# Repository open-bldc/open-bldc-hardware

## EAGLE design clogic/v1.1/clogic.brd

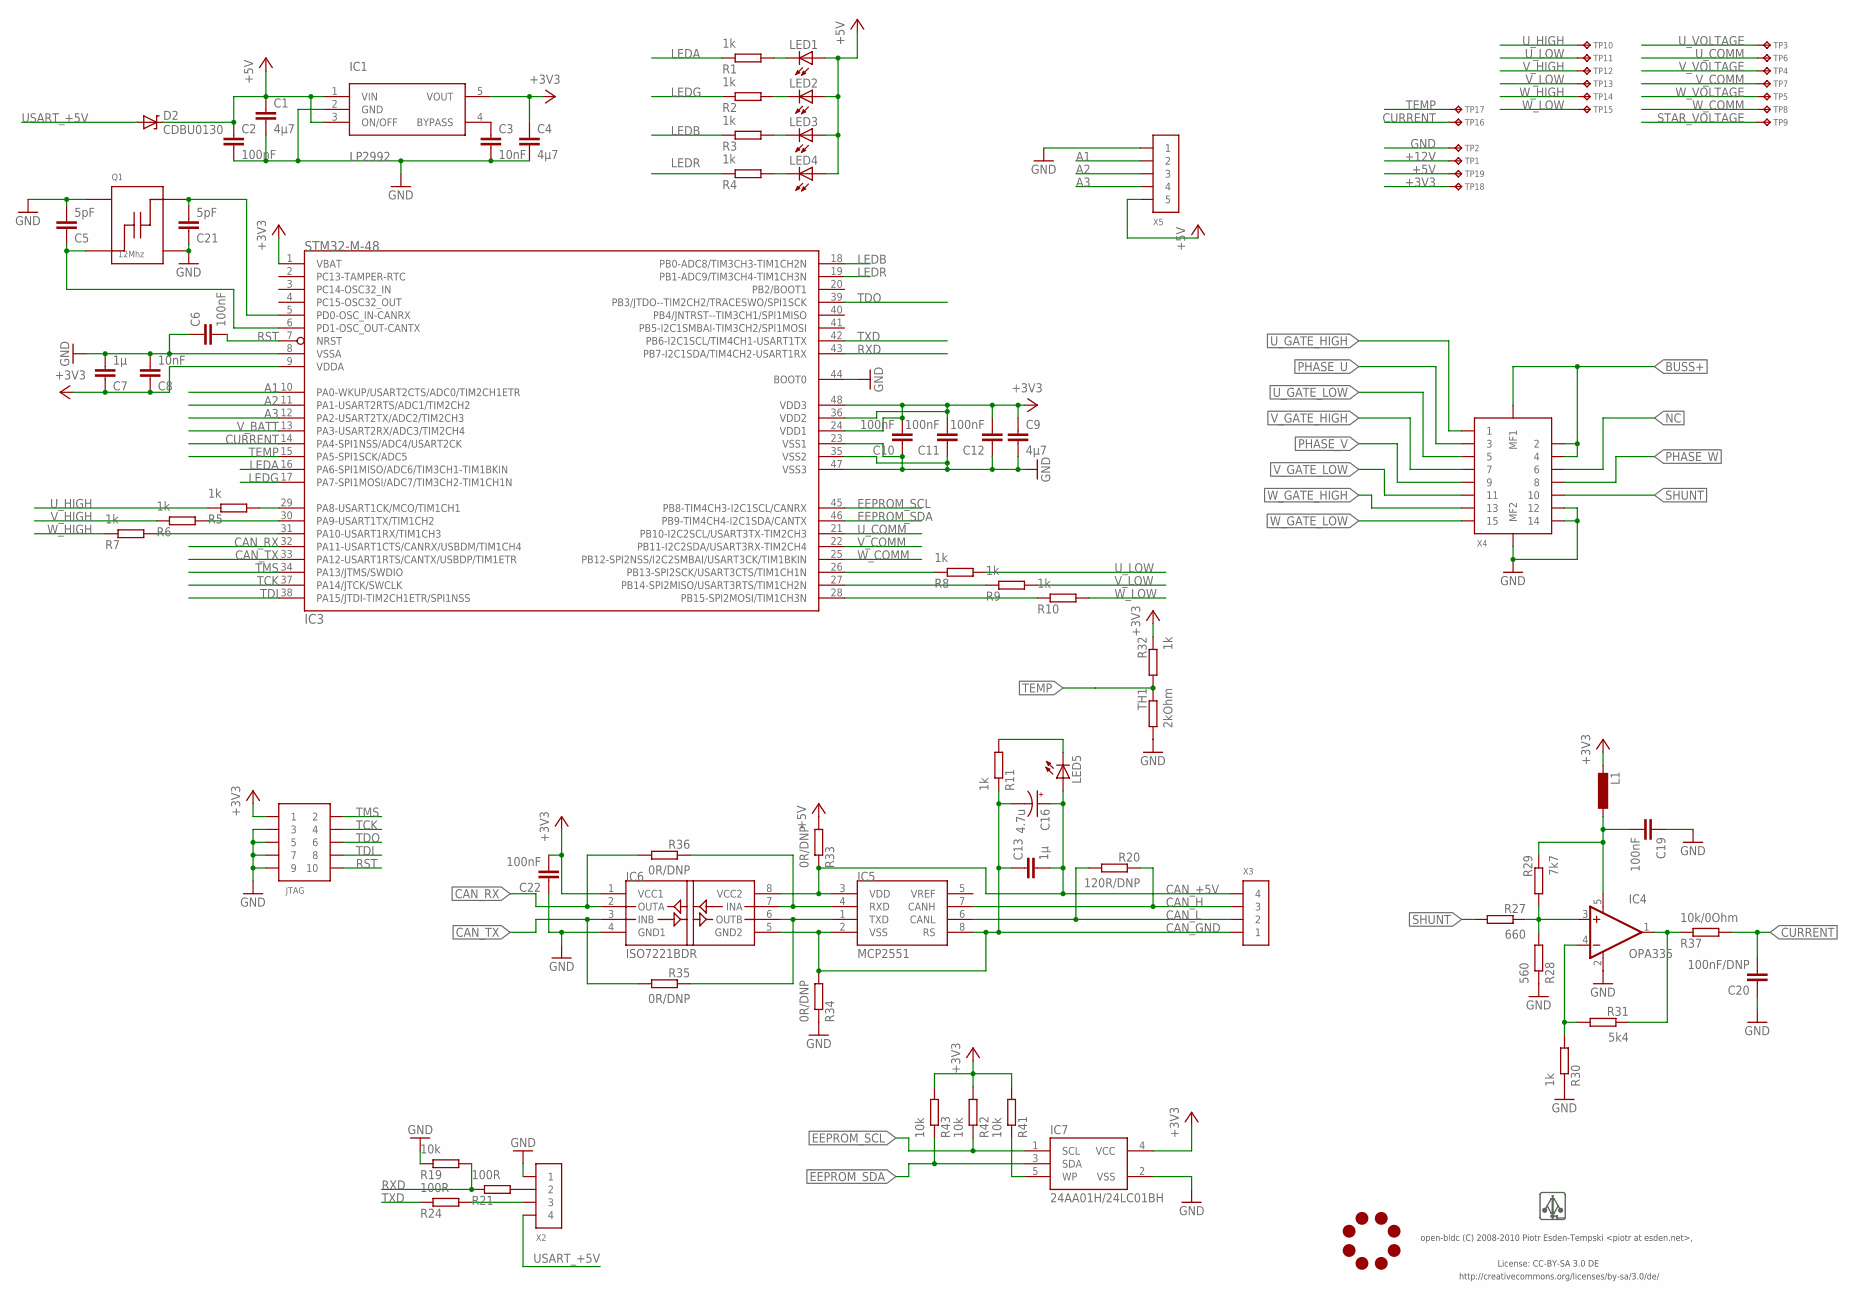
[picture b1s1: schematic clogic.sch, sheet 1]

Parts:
C1, C4, C9: 4µ7; 0603-CAP
C2, C6, C10, C11, C12, C19, C22: 100nF; 0603-CAP
C3, C8: 10nF; 0603-CAP
C5, C21: 5pF; 0603-CAP
C7, C13: 1µ; 0603-CAP
C16: 4.7u; CAP_0805TANT_F95
C20: 100nF/DNP; 0603-CAP
D2: CDBU0130; 0603-LED
IC1: LP2992; SOT23-5
IC3: STM32-M-48; LQFP48
IC4: OPA335; SOT23-5
IC5: MCP2551; SO8
IC6: ISO7221BDR; SO8
IC7: 24AA01H/24LC01BH; SOT23-5
JL1: JOBY_LOGO-6MIL; JOBY_LOGO_6MIL
JTAG: CONN_5-2-FTSH-V; FTSH-105-DV
L1: INDUCTOR-0603; 0603-IND
LED1: AMBER; 0603-LED
LED2: GREEN; 0603-LED
LED3: BLUE; 0603-LED
LED4: RED; 0603-LED
LED5: WHITE; 0603-LED
Q1: 12Mhz; ABM8
R1, R2, R3, R4, R5, R6, R7, R8, R9, R10, R11, R30, R32: 1k; 0603-RES
R19, R41, R42, R43: 10k; 0603-RES
R20: 120R/DNP; 0603-RES
R21, R24: 100R; 0603-RES
R27: 660; 0603-RES
R28: 560; 0603-RES
R29: 7k7; 0603-RES
R31: 5k4; 0603-RES
R33, R34, R35, R36: 0R/DNP; 0603-RES
R37: 10k/0Ohm; 0603-RES
TH1: 2kOhm; 0603-RES
TP1, TP2, TP3, TP4, TP5, TP6, TP7, TP8, TP9, TP10, TP11, TP12, TP13, TP14, TP15, TP16, TP17, TP18, TP19: TP-09RSMD; TP09R
U$1: LOGO
X2, X3: CONN_4-1-53261; PB-53261-04
X4: CONN_15-2-2MT-DF9; DF9-15
X5: CONN_5-1-53261; PB-53261-05

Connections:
+3V3: C4.P$1 (1), C7.P$1 (1), C8.P$1 (1), C9.P$1 (1), C10.P$2 (2), C11.P$2 (2), C12.P$2 (2), C22.P$2 (2), IC1.5 (VOUT), IC3.1 (VBAT), IC3.9 (VDDA), IC3.24 (VDD1), IC3.36 (VDD2), IC3.48 (VDD3), IC6.1 (VCC1), IC7.4 (VCC), JTAG.1, L1.P$2 (2), R32.P$1 (1), R41.P$2 (2), R42.P$2 (2), R43.P$2 (2), TP18.P$1
+5V: C1.P$1 (1), C2.P$1 (1), D2.C, IC1.1 (VIN), IC1.3 (ON/OFF), LED1.A, LED2.A, LED3.A, LED4.A, R33.P$2 (2), TP19.P$1, X5.5; also elsewhere on the board
+12V: TP1.P$1; also elsewhere on the board
A1: IC3.10 (PA0-WKUP/USART2CTS/ADC0/TIM2CH1ETR), X5.2; also elsewhere on the board
A2: IC3.11 (PA1-USART2RTS/ADC1/TIM2CH2), X5.3; also elsewhere on the board
A3: IC3.12 (PA2-USART2TX/ADC2/TIM2CH3), X5.4; also elsewhere on the board
BUSS+: X4.2, X4.4, X4.MF1; also elsewhere on the board
CAN_+5V: C13.P$2 (2), C16.P$1 (+), IC5.3 (VDD), IC6.8 (VCC2), LED5.A, R33.P$1 (1), X3.4
CAN_GND: C13.P$1 (1), C16.P$2 (-), IC5.2 (VSS), IC5.8 (RS), IC6.5 (GND2), R11.P$1 (1), R34.P$2 (2), X3.1
CAN_H: IC5.7 (CANH), R20.P$1 (1), X3.3
CAN_L: IC5.6 (CANL), R20.P$2 (2), X3.2
CAN_RX: IC3.32 (PA11-USART1CTS/CANRX/USBDM/TIM1CH4), IC6.2 (OUTA), R36.P$2 (2)
CAN_TX: IC3.33 (PA12-USART1RTS/CANTX/USBDP/TIM1ETR), IC6.3 (INB), R35.P$2 (2)
CURRENT: C20.P$2 (2), IC3.14 (PA4-SPI1NSS/ADC4/USART2CK), R37.P$2 (2), TP16.P$1
CURRENT_RAW: IC4.1 (OUT), R31.P$1 (1), R37.P$1 (1)
EEPROM_SCL: IC3.45 (PB8-TIM4CH3-I2C1SCL/CANRX), IC7.1 (SCL), R42.P$1 (1)
EEPROM_SDA: IC3.46 (PB9-TIM4CH4-I2C1SDA/CANTX), IC7.3 (SDA), R43.P$1 (1)
GND: C1.P$2 (2), C2.P$2 (2), C3.P$2 (2), C4.P$2 (2), C5.P$2 (2), C6.P$1 (1), C7.P$2 (2), C8.P$2 (2), C9.P$2 (2), C10.P$1 (1), C11.P$1 (1), C12.P$1 (1), C19.P$1 (1), C20.P$1 (1), C21.P$1 (1), C22.P$1 (1), IC1.2 (GND), IC3.8 (VSSA), IC3.23 (VSS1), IC3.35 (VSS2), IC3.44 (BOOT0), IC3.47 (VSS3), IC4.2 (V-), IC6.4 (GND1), IC7.2 (VSS), JTAG.3, JTAG.5, JTAG.7, JTAG.9, Q1.P$2, Q1.P$4, R19.P$1 (1), R28.P$1 (1), R30.P$1 (1), R34.P$1 (1), TH1.P$2 (2), TP2.P$1, X2.1, X4.12, X4.14, X4.MF2, X5.1; also elsewhere on the board
LEDA: IC3.16 (PA6-SPI1MISO/ADC6/TIM3CH1-TIM1BKIN), R1.P$1 (1)
LEDB: IC3.18 (PB0-ADC8/TIM3CH3-TIM1CH2N), R3.P$1 (1)
LEDG: IC3.17 (PA7-SPI1MOSI/ADC7/TIM3CH2-TIM1CH1N), R2.P$1 (1)
LEDR: IC3.19 (PB1-ADC9/TIM3CH4-TIM1CH3N), R4.P$1 (1)
unnamed: LED5.C, R11.P$2 (2)
unnamed: LED1.C, R1.P$2 (2)
unnamed: LED4.C, R4.P$2 (2)
unnamed: LED3.C, R3.P$2 (2)
unnamed: R21.P$2 (2), X2.2
unnamed: C19.P$2 (2), IC4.5 (V+), L1.P$1 (1), R29.P$1 (1)
unnamed: LED2.C, R2.P$2 (2)
unnamed: IC4.3 (+IN), R27.P$1 (1), R28.P$2 (2), R29.P$2 (2)
unnamed: IC4.4 (-IN), R30.P$2 (2), R31.P$2 (2)
unnamed: IC5.1 (TXD), IC6.6 (OUTB), R35.P$1 (1)
unnamed: IC5.4 (RXD), IC6.7 (INA), R36.P$1 (1)
unnamed: C5.P$1 (1), IC3.6 (PD1-OSC_OUT-CANTX), Q1.P$1
unnamed: IC7.5 (WP), R41.P$1 (1)
unnamed: C21.P$2 (2), IC3.5 (PD0-OSC_IN-CANRX), Q1.P$3
unnamed: R24.P$2 (2), X2.3
unnamed: C3.P$1 (1), IC1.4 (BYPASS)
unnamed: IC3.26 (PB13-SPI2SCK/USART3CTS/TIM1CH1N), R8.P$1 (1)
unnamed: IC3.27 (PB14-SPI2MISO/USART3RTS/TIM1CH2N), R9.P$1 (1)
unnamed: IC3.28 (PB15-SPI2MOSI/TIM1CH3N), R10.P$1 (1)
unnamed: IC3.29 (PA8-USART1CK/MCO/TIM1CH1), R5.P$2 (2)
unnamed: IC3.30 (PA9-USART1TX/TIM1CH2), R6.P$2 (2)
unnamed: IC3.31 (PA10-USART1RX/TIM1CH3), R7.P$2 (2)
NC: X4.6
PHASE_U: X4.3; also elsewhere on the board
PHASE_V: X4.9; also elsewhere on the board
PHASE_W: X4.8; also elsewhere on the board
RST: C6.P$2 (2), IC3.7 (NRST), JTAG.10
RXD: IC3.43 (PB7-I2C1SDA/TIM4CH2-USART1RX), R19.P$2 (2), R21.P$1 (1)
SHUNT: R27.P$2 (2), X4.10
STAR_VOLTAGE: TP9.P$1; also elsewhere on the board
TCK: IC3.37 (PA14/JTCK/SWCLK), JTAG.4
TDI: IC3.38 (PA15/JTDI-TIM2CH1ETR/SPI1NSS), JTAG.8
TDO: IC3.39 (PB3/JTDO--TIM2CH2/TRACESWO/SPI1SCK), JTAG.6
TEMP: IC3.15 (PA5-SPI1SCK/ADC5), R32.P$2 (2), TH1.P$1 (1), TP17.P$1
TMS: IC3.34 (PA13/JTMS/SWDIO), JTAG.2
TXD: IC3.42 (PB6-I2C1SCL/TIM4CH1-USART1TX), R24.P$1 (1)
USART_+5V: D2.A, X2.4
U_COMM: IC3.21 (PB10-I2C2SCL/USART3TX-TIM2CH3), TP6.P$1; also elsewhere on the board
U_GATE_HIGH: X4.1; also elsewhere on the board
U_GATE_LOW: X4.5; also elsewhere on the board
U_HIGH: R5.P$1 (1), TP10.P$1; also elsewhere on the board
U_LOW: R8.P$2 (2), TP11.P$1; also elsewhere on the board
U_VOLTAGE: TP3.P$1; also elsewhere on the board
V_BATT: IC3.13 (PA3-USART2RX/ADC3/TIM2CH4); also elsewhere on the board
V_COMM: IC3.22 (PB11-I2C2SDA/USART3RX-TIM2CH4), TP7.P$1; also elsewhere on the board
V_GATE_HIGH: X4.7; also elsewhere on the board
V_GATE_LOW: X4.11; also elsewhere on the board
V_HIGH: R6.P$1 (1), TP12.P$1; also elsewhere on the board
V_LOW: R9.P$2 (2), TP13.P$1; also elsewhere on the board
V_VOLTAGE: TP4.P$1; also elsewhere on the board
W_COMM: IC3.25 (PB12-SPI2NSS/I2C2SMBAI/USART3CK/TIM1BKIN), TP8.P$1; also elsewhere on the board
W_GATE_HIGH: X4.13; also elsewhere on the board
W_GATE_LOW: X4.15; also elsewhere on the board
W_HIGH: R7.P$1 (1), TP14.P$1; also elsewhere on the board
W_LOW: R10.P$2 (2), TP15.P$1; also elsewhere on the board
W_VOLTAGE: TP5.P$1; also elsewhere on the board

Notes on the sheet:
License: CC-BY-SA 3.0 DE
http://creativecommons.org/licenses/by-sa/3.0/de/
open-bldc (C) 2008-2010 Piotr Esden-Tempski <piotr at esden.net>,

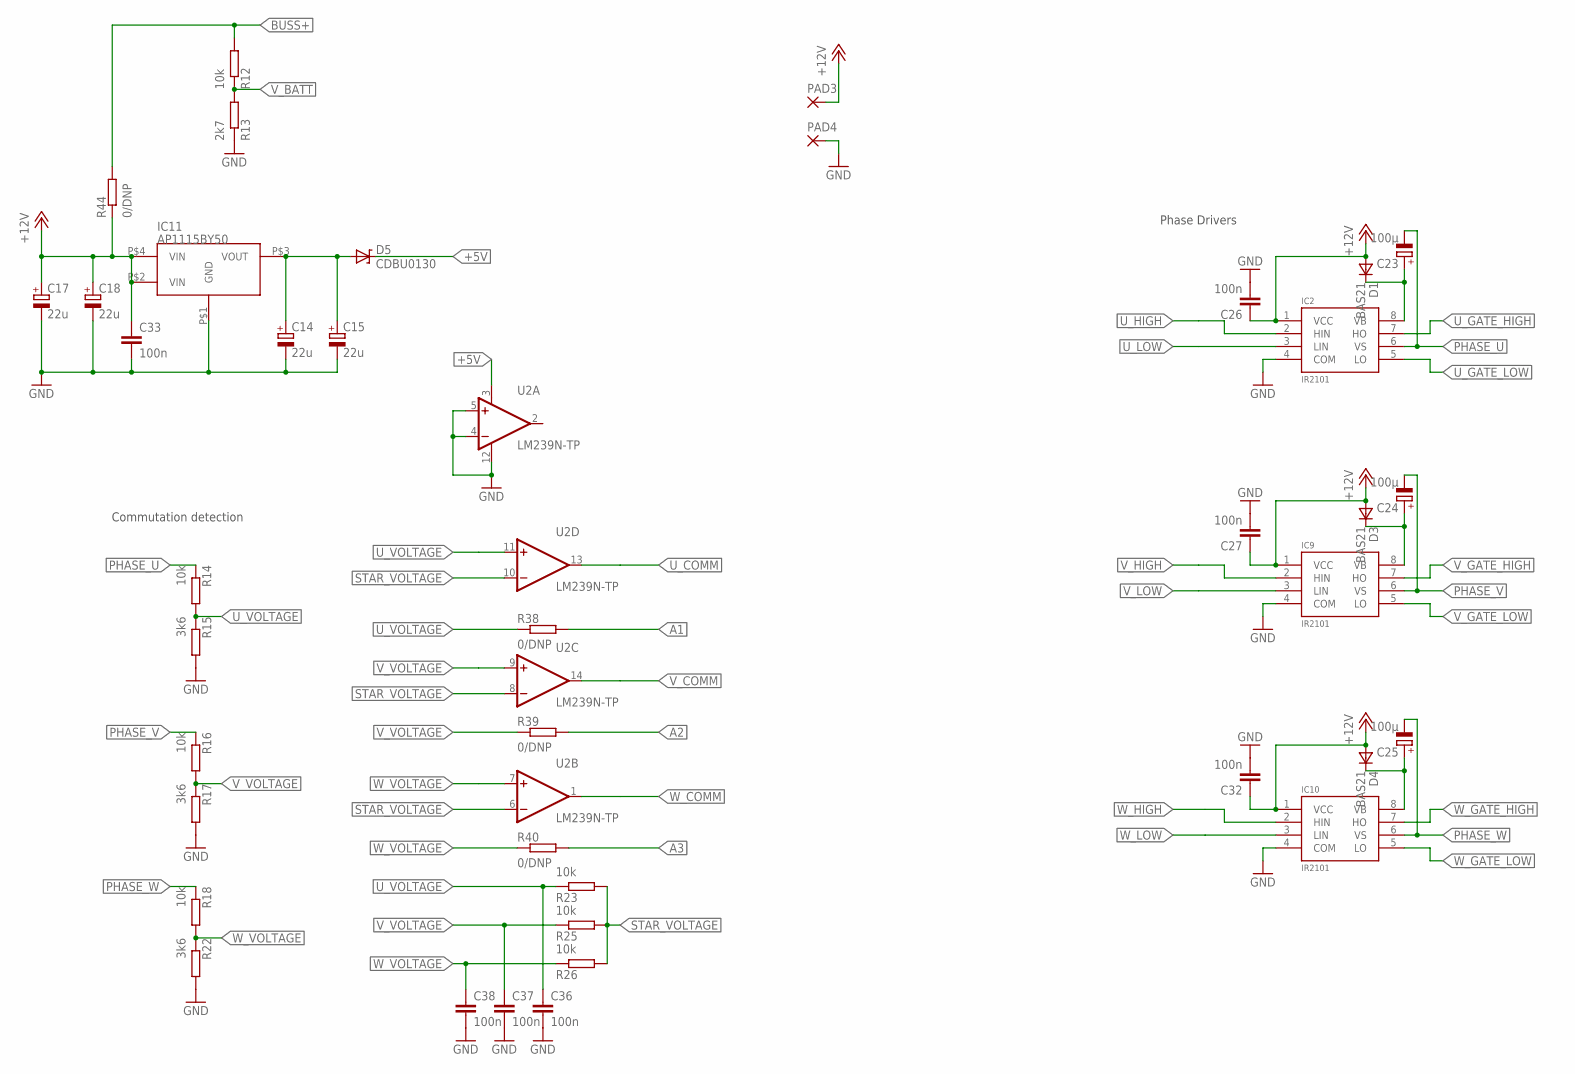
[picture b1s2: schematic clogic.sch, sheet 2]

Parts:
C14, C15, C17, C18: 22u; 0805-POL-CAP
C23, C24, C25: 100µ; 0805-POL-CAP
C26, C27, C32, C33, C36, C37, C38: 100n; 0603-CAP
D1, D3, D4: BAS21; SOT-23
D5: CDBU0130; 0603-LED
IC2, IC9, IC10: IR2101; SO-8
IC11: AP1115BY50; SOT89
PAD3, PAD4: SMD5; SMD2,54-5,08
R12, R14, R16, R18, R23, R25, R26: 10k; 0603-RES
R13: 2k7; 0603-RES
R15, R17, R22: 3k6; 0603-RES
R38, R39, R40, R44: 0/DNP; 0603-RES
U2: LM239N-TP; TSSOP_14

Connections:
+5V: D5.C, U2.3 (V+); also elsewhere on the board
+5VOUT: C14.+, C15.+, D5.A, IC11.P$3 (VOUT)
+12V: C17.+, C18.+, C26.P$1 (1), C27.P$1 (1), C32.P$1 (1), C33.P$1 (1), D1.3 (A), D3.3 (A), D4.3 (A), IC2.1 (VCC), IC9.1 (VCC), IC10.1 (VCC), IC11.P$2 (VIN), IC11.P$4 (VIN), PAD3.1, R44.P$1 (1); also elsewhere on the board
A1: R38.P$2 (2); also elsewhere on the board
A2: R39.P$2 (2); also elsewhere on the board
A3: R40.P$2 (2); also elsewhere on the board
BUSS+: R12.P$2 (2), R44.P$2 (2); also elsewhere on the board
GND: C14.-, C15.-, C17.-, C18.-, C26.P$2 (2), C27.P$2 (2), C32.P$2 (2), C33.P$2 (2), C36.P$2 (2), C37.P$2 (2), C38.P$2 (2), IC2.4 (COM), IC9.4 (COM), IC10.4 (COM), IC11.P$1 (GND), PAD4.1, R13.P$1 (1), R15.P$2 (2), R17.P$2 (2), R22.P$2 (2), U2.4 (-IN), U2.5 (+IN), U2.12 (V-); also elsewhere on the board
unnamed: C23.+, D1.1 (C), IC2.8 (VB)
unnamed: C24.+, D3.1 (C), IC9.8 (VB)
unnamed: C25.+, D4.1 (C), IC10.8 (VB)
PHASE_U: C23.-, IC2.6 (VS), R14.P$1 (1); also elsewhere on the board
PHASE_V: C24.-, IC9.6 (VS), R16.P$1 (1); also elsewhere on the board
PHASE_W: C25.-, IC10.6 (VS), R18.P$1 (1); also elsewhere on the board
STAR_VOLTAGE: R23.P$2 (2), R25.P$2 (2), R26.P$2 (2), U2.6 (-IN), U2.8 (-IN), U2.10 (-IN); also elsewhere on the board
U_COMM: U2.13 (OUT); also elsewhere on the board
U_GATE_HIGH: IC2.7 (HO); also elsewhere on the board
U_GATE_LOW: IC2.5 (LO); also elsewhere on the board
U_HIGH: IC2.2 (HIN); also elsewhere on the board
U_LOW: IC2.3 (LIN); also elsewhere on the board
U_VOLTAGE: C36.P$1 (1), R14.P$2 (2), R15.P$1 (1), R23.P$1 (1), R38.P$1 (1), U2.11 (+IN); also elsewhere on the board
V_BATT: R12.P$1 (1), R13.P$2 (2); also elsewhere on the board
V_COMM: U2.14 (OUT); also elsewhere on the board
V_GATE_HIGH: IC9.7 (HO); also elsewhere on the board
V_GATE_LOW: IC9.5 (LO); also elsewhere on the board
V_HIGH: IC9.2 (HIN); also elsewhere on the board
V_LOW: IC9.3 (LIN); also elsewhere on the board
V_VOLTAGE: C37.P$1 (1), R16.P$2 (2), R17.P$1 (1), R25.P$1 (1), R39.P$1 (1), U2.9 (+IN); also elsewhere on the board
W_COMM: U2.1 (OUT); also elsewhere on the board
W_GATE_HIGH: IC10.7 (HO); also elsewhere on the board
W_GATE_LOW: IC10.5 (LO); also elsewhere on the board
W_HIGH: IC10.2 (HIN); also elsewhere on the board
W_LOW: IC10.3 (LIN); also elsewhere on the board
W_VOLTAGE: C38.P$1 (1), R18.P$2 (2), R22.P$1 (1), R26.P$1 (1), R40.P$1 (1), U2.7 (+IN); also elsewhere on the board

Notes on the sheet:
Phase Drivers
Commutation detection

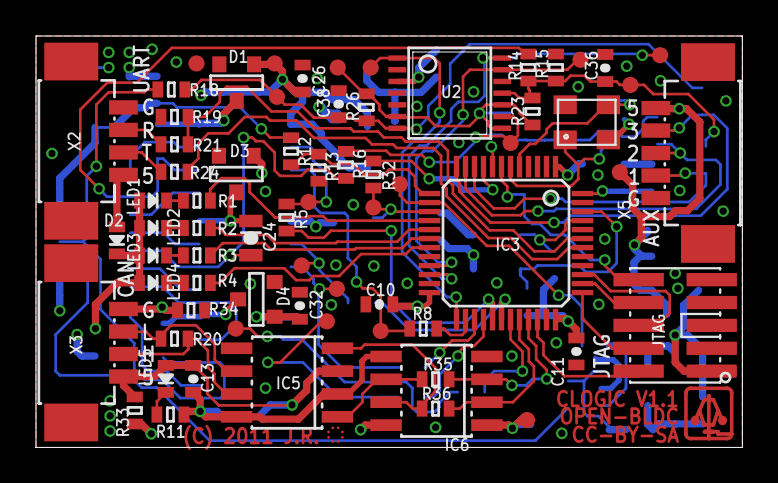
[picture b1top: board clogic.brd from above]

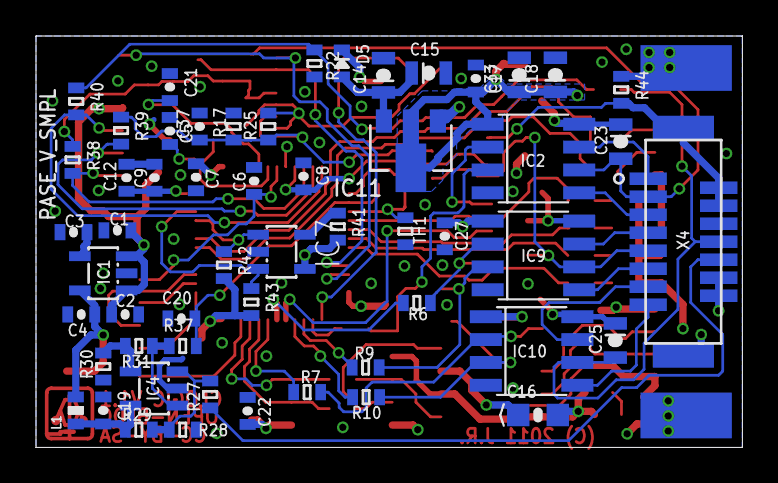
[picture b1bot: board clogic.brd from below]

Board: 4 copper layers, 39.2 x 22.9 mm, 129 parts (57 on the bottom side), 81 nets.

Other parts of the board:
DRILEGEND: DRILEGEND

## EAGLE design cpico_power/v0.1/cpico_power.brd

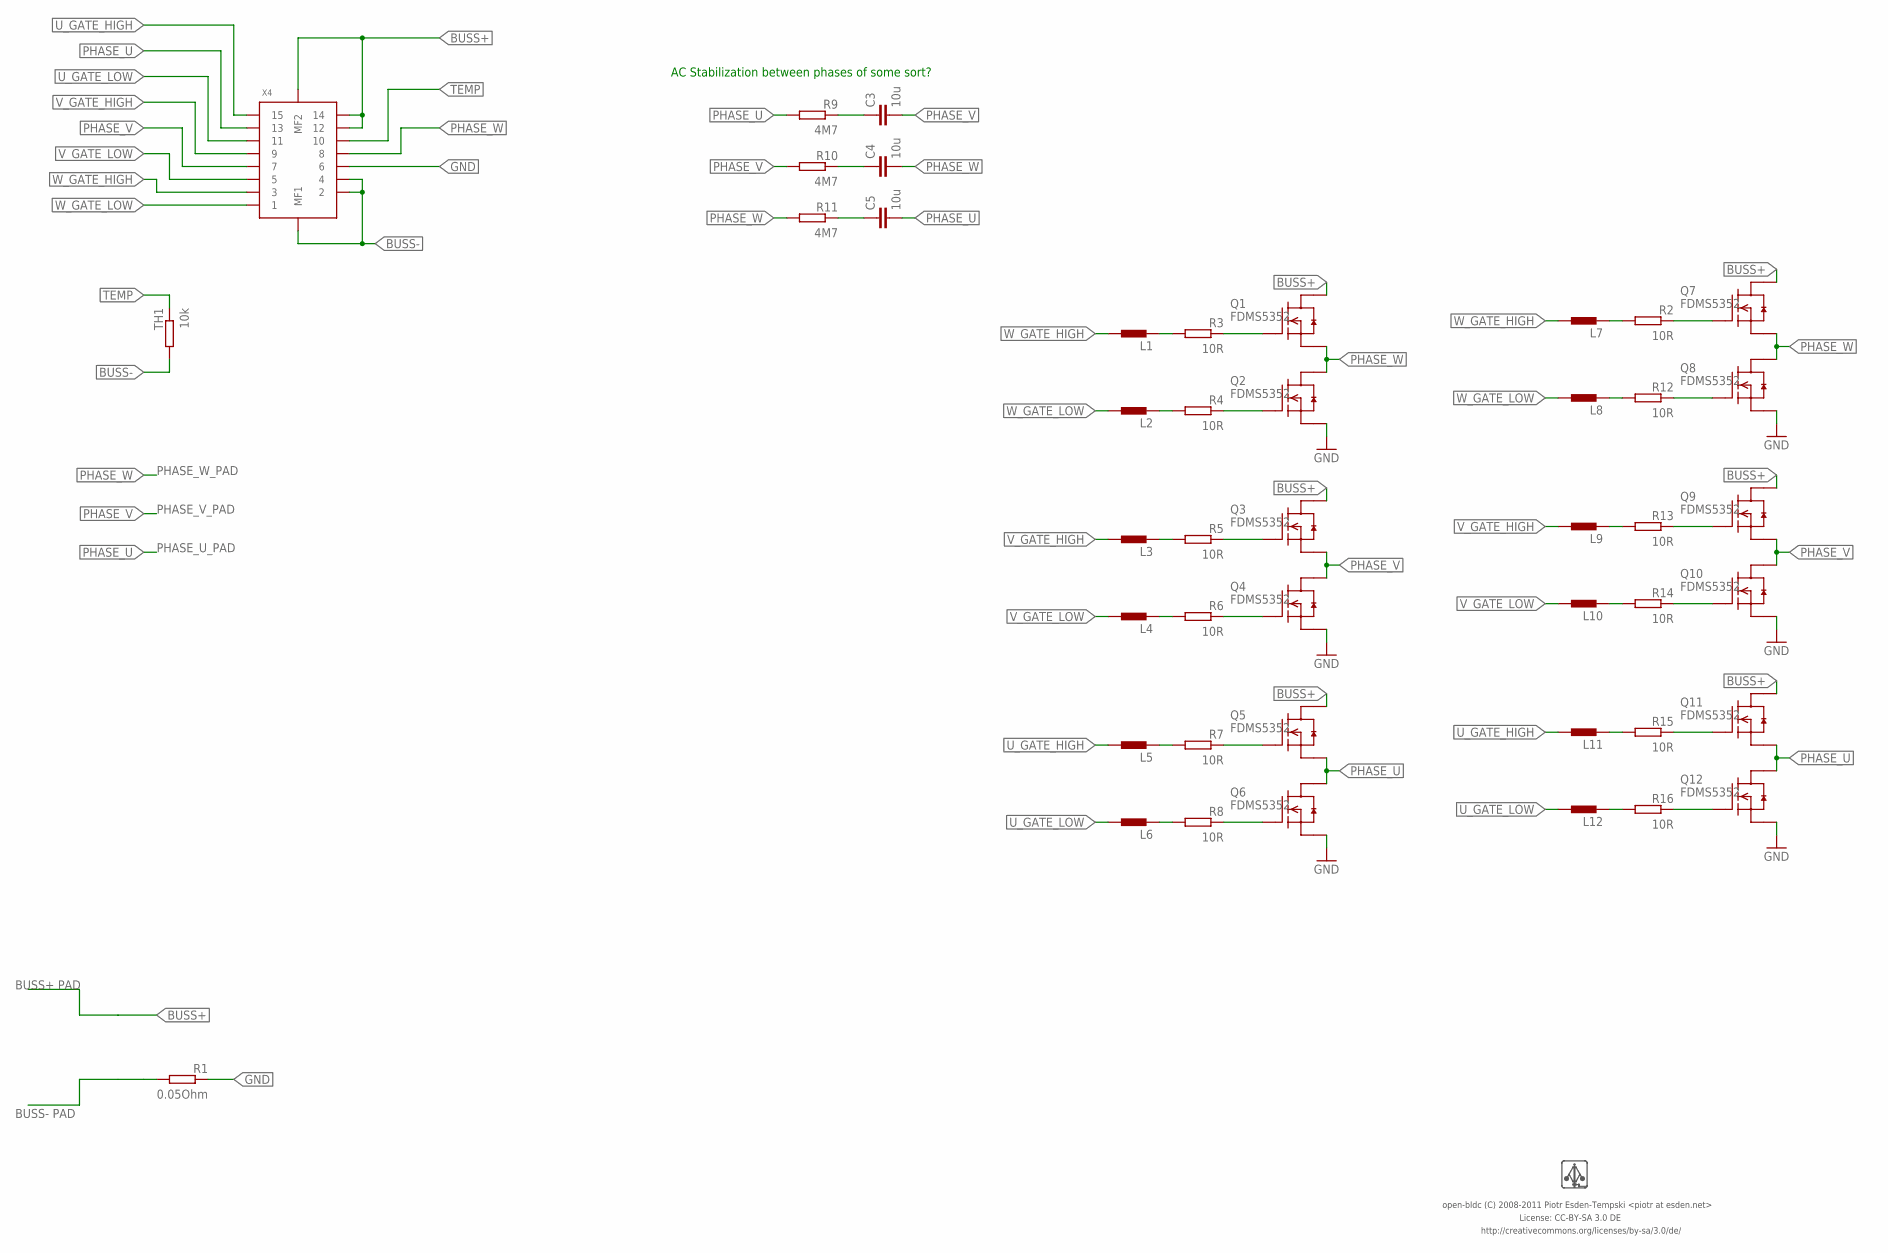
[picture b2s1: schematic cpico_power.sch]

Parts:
C3, C4, C5: 10u; 0603-CAP
L1, L2, L3, L4, L5, L6, L7, L8, L9, L10, L11, L12: INDUCTOR-0402; 0402-IND
Q1, Q2, Q3, Q4, Q5, Q6, Q7, Q8, Q9, Q10, Q11, Q12: FDMS5352; MSL1
R1: 0.05Ohm; 1206-RES
R2, R3, R4, R5, R6, R7, R8, R12, R13, R14, R15, R16: 10R; 0402-RES
R9, R10, R11: 4M7; 0603-RES
TH1: 10k; 0603-RES
U$2: LOGO-NORM; LOGO
X4: CONN_15-2-2MT-DF9; DF9-15

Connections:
BUSS+: Q1.3 (D), Q3.3 (D), Q5.3 (D), Q7.3 (D), Q9.3 (D), Q11.3 (D), X4.12, X4.14, X4.MF2
BUSS-: R1.P$2 (2), TH1.P$2 (2), X4.2, X4.4, X4.MF1
GND: Q2.1 (S), Q4.1 (S), Q6.1 (S), Q8.1 (S), Q10.1 (S), Q12.1 (S), R1.P$1 (1), X4.6
unnamed: Q1.2 (G), R3.P$1 (1)
unnamed: C3.P$1 (1), R9.P$1 (1)
unnamed: C4.P$1 (1), R10.P$1 (1)
unnamed: C5.P$1 (1), R11.P$1 (1)
unnamed: Q2.2 (G), R4.P$1 (1)
unnamed: Q3.2 (G), R5.P$1 (1)
unnamed: Q4.2 (G), R6.P$1 (1)
unnamed: Q5.2 (G), R7.P$1 (1)
unnamed: Q6.2 (G), R8.P$1 (1)
unnamed: L1.P$2 (2), R3.P$2 (2)
unnamed: L2.P$2 (2), R4.P$2 (2)
unnamed: L3.P$2 (2), R5.P$2 (2)
unnamed: L4.P$2 (2), R6.P$2 (2)
unnamed: L5.P$2 (2), R7.P$2 (2)
unnamed: L6.P$2 (2), R8.P$2 (2)
unnamed: L7.P$2 (2), R2.P$2 (2)
unnamed: L8.P$2 (2), R12.P$2 (2)
unnamed: L9.P$2 (2), R13.P$2 (2)
unnamed: L10.P$2 (2), R14.P$2 (2)
unnamed: L11.P$2 (2), R15.P$2 (2)
unnamed: L12.P$2 (2), R16.P$2 (2)
unnamed: Q7.2 (G), R2.P$1 (1)
unnamed: Q8.2 (G), R12.P$1 (1)
unnamed: Q9.2 (G), R13.P$1 (1)
unnamed: Q10.2 (G), R14.P$1 (1)
unnamed: Q11.2 (G), R15.P$1 (1)
unnamed: Q12.2 (G), R16.P$1 (1)
PHASE_U: C5.P$2 (2), Q5.1 (S), Q6.3 (D), Q11.1 (S), Q12.3 (D), R9.P$2 (2), X4.13
PHASE_V: C3.P$2 (2), Q3.1 (S), Q4.3 (D), Q9.1 (S), Q10.3 (D), R10.P$2 (2), X4.7
PHASE_W: C4.P$2 (2), Q1.1 (S), Q2.3 (D), Q7.1 (S), Q8.3 (D), R11.P$2 (2), X4.8
TEMP: TH1.P$1 (1), X4.10
U_GATE_HIGH: L5.P$1 (1), L11.P$1 (1), X4.15
U_GATE_LOW: L6.P$1 (1), L12.P$1 (1), X4.11
V_GATE_HIGH: L3.P$1 (1), L9.P$1 (1), X4.9
V_GATE_LOW: L4.P$1 (1), L10.P$1 (1), X4.5
W_GATE_HIGH: L1.P$1 (1), L7.P$1 (1), X4.3
W_GATE_LOW: L2.P$1 (1), L8.P$1 (1), X4.1

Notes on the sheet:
License: CC-BY-SA 3.0 DE
http://creativecommons.org/licenses/by-sa/3.0/de/
open-bldc (C) 2008-2011 Piotr Esden-Tempski <piotr at esden.net>
AC Stabilization between phases of some sort?
BUSS+ PAD
BUSS- PAD
PHASE_W_PAD
PHASE_V_PAD
PHASE_U_PAD

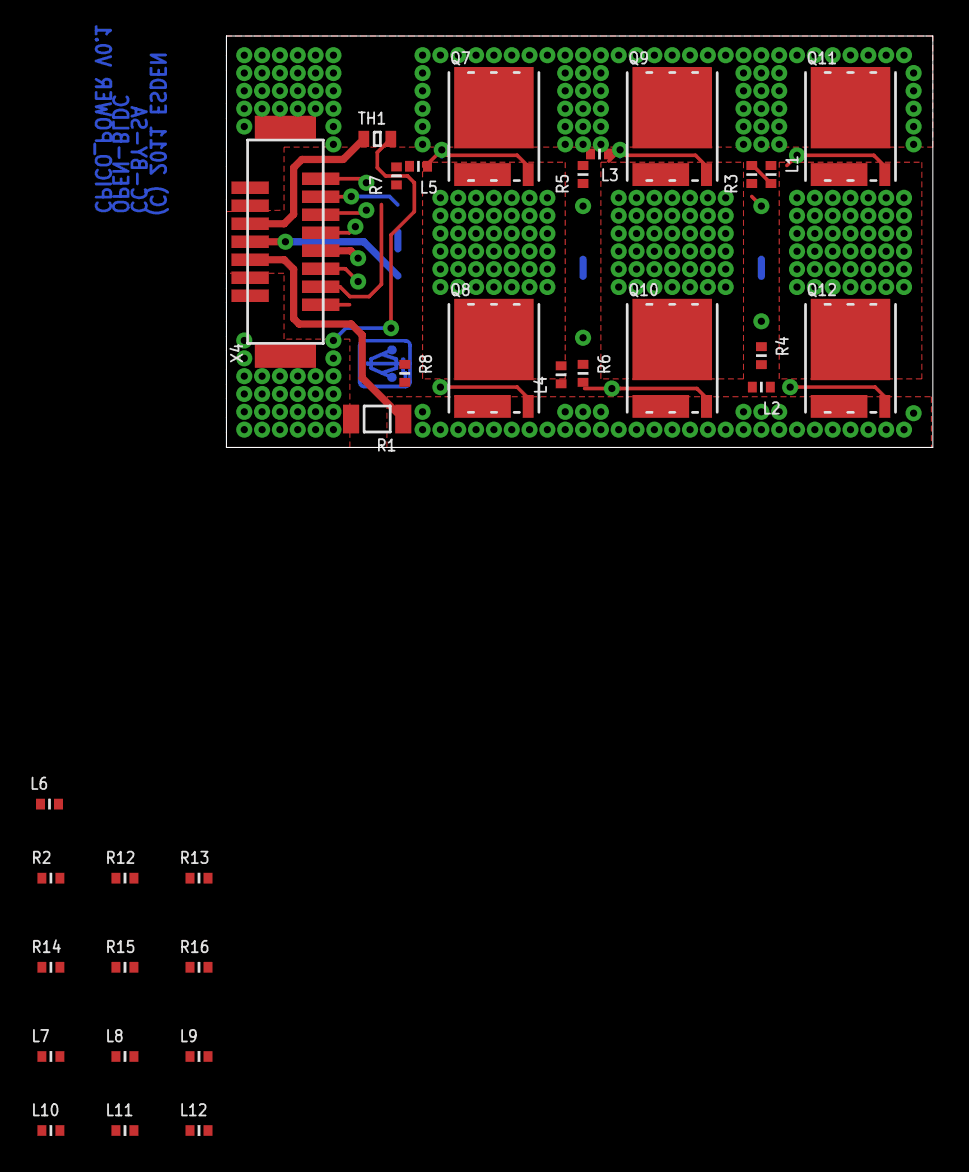
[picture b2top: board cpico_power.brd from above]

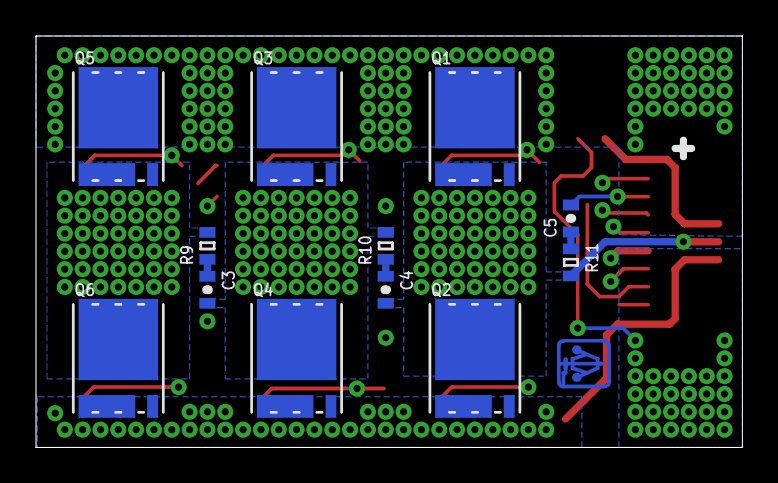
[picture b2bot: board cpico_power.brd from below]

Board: 4 copper layers, 39.2 x 22.9 mm, 46 parts (13 on the bottom side), 40 nets.

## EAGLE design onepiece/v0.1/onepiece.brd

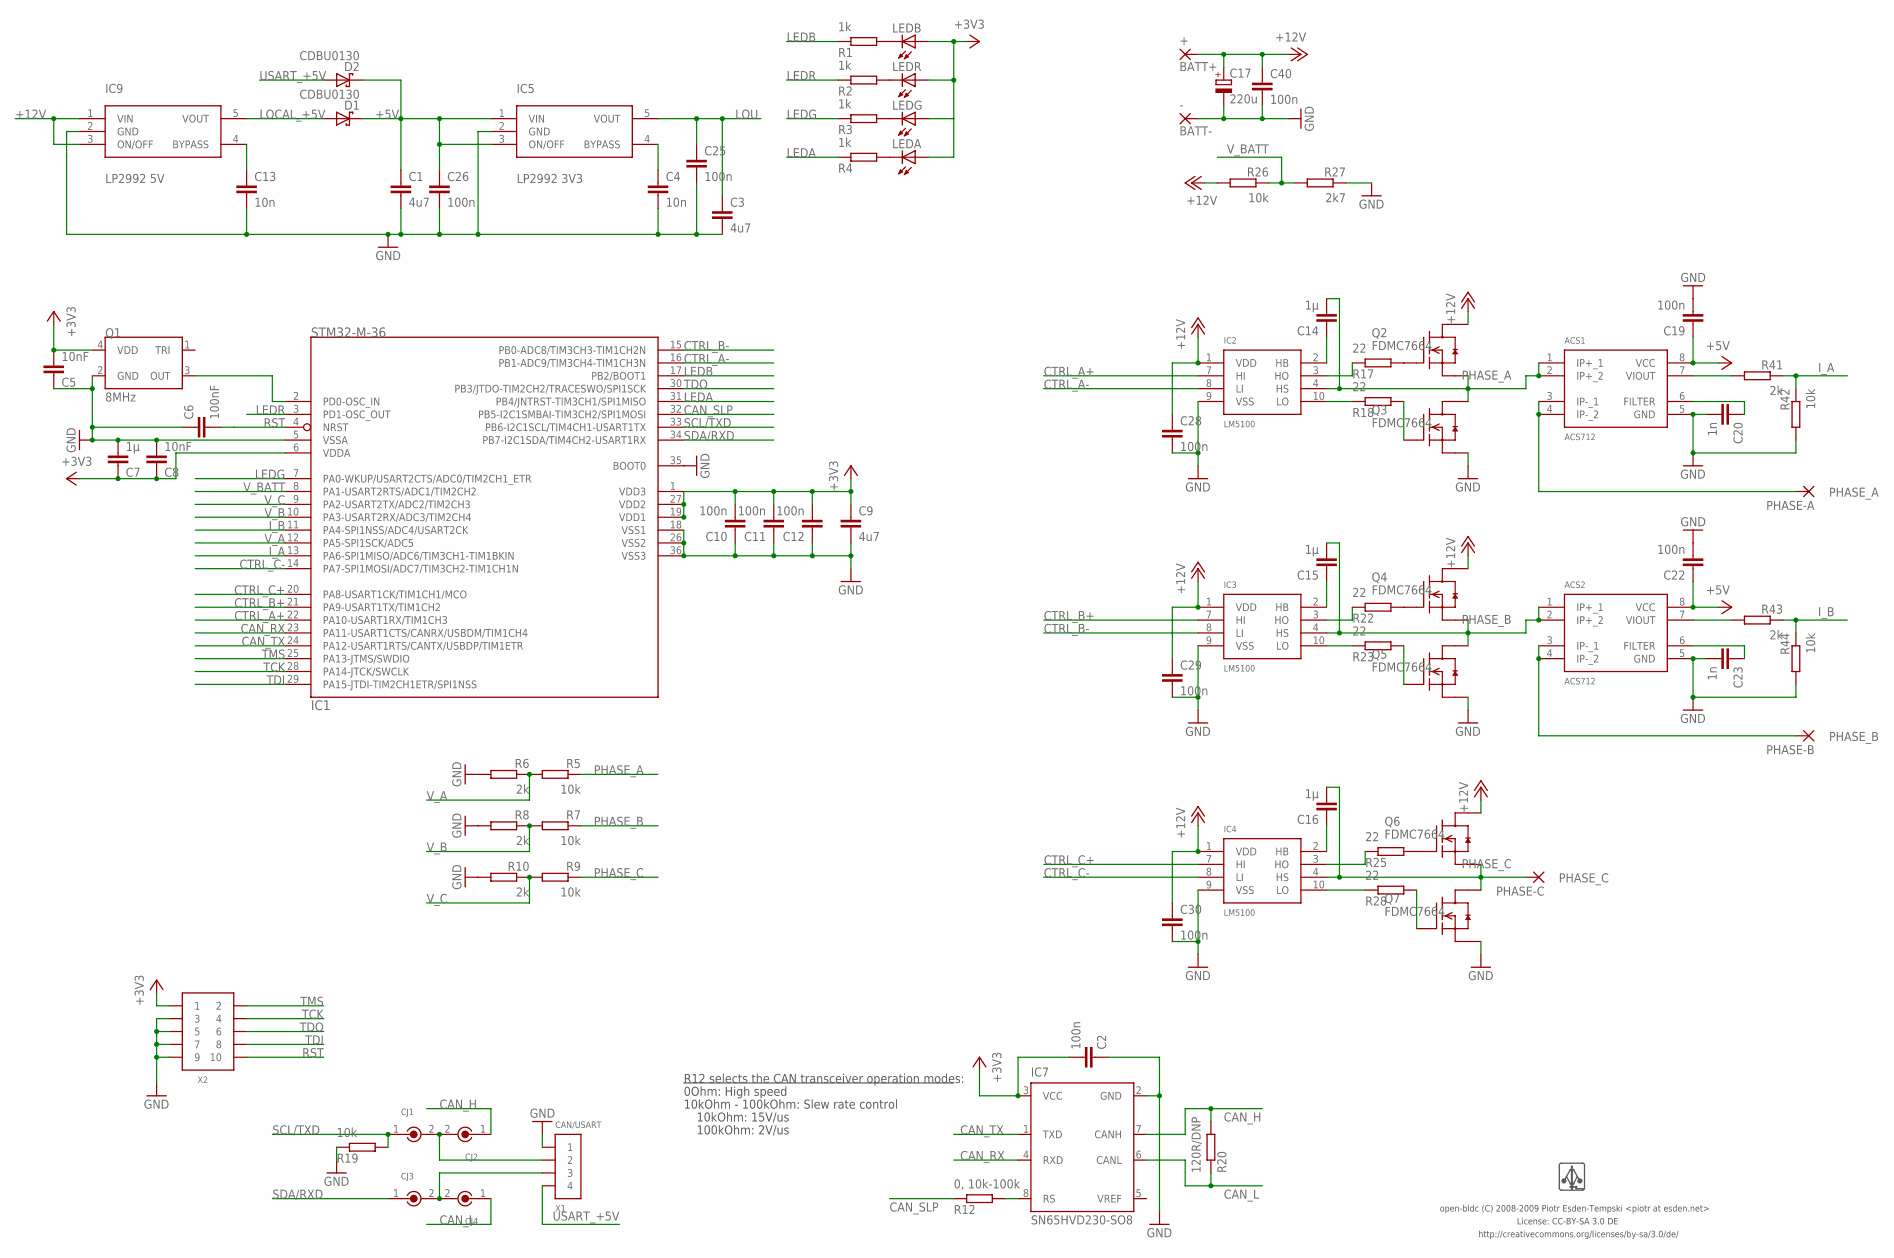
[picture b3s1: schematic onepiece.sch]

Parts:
+: BATT+; SMD2,54-5,08
-: BATT-; SMD2,54-5,08
ACS1, ACS2: ACS712; SO8
C1, C3, C9: 4u7; 0603-CAP
C2, C10, C11, C12, C19, C22, C25, C26, C28, C29, C30, C40: 100n; 0603-CAP
C4, C13: 10n; 0603-CAP
C5, C8: 10nF; 0603-CAP
C6: 100nF; 0603-CAP
C7, C14, C15, C16: 1µ; 0603-CAP
C17: 220u; 7343/D
C20, C23: 1n; 0603-CAP
CJ1, CJ2, CJ3, CJ4: CIRC_JMP
D1, D2: CDBU0130; 0603-LED
IC1: STM32-M-36; VFQFPN36-LP
IC2, IC3, IC4: LM5100; LLP-10
IC5: LP2992 3V3; SOT23-5
IC7: SN65HVD230-SO8; SO8
IC9: LP2992 5V; SOT23-5
LEDA: AMBER; 0603-LED
LEDB: BLUE; 0603-LED
LEDG: GREEN; 0603-LED
LEDR: RED; 0603-LED
PHASE-A: PHASE_A; SMD2,54-5,08
PHASE-B: PHASE_B; SMD2,54-5,08
PHASE-C: PHASE_C; SMD2,54-5,08
Q1: 8MHz; ASE_OSCILLATOR
Q2, Q3, Q4, Q5, Q6, Q7: FDMC7664; MLP33
R1, R2, R3, R4: 1k; 0603-RES
R5, R7, R9, R19, R26, R42, R44: 10k; 0603-RES
R6, R8, R10, R41, R43: 2k; 0603-RES
R12: 0, 10k-100k; 0603-RES
R17, R18, R22, R23, R25, R28: 22; 0603-RES
R20: 120R/DNP; 0603-RES
R27: 2k7; 0603-RES
U$1: LOGO; LOGO_SMALL
X1: CAN/USART; PB-53261-04
X2: PIN_HDR_EDG_1.27MM_5-2; PIN_HDR_1.27MM_SMD_DH_10

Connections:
+5V: ACS1.8 (VCC), ACS2.8 (VCC), C1.P$1 (1), C19.P$1 (1), C22.P$1 (1), C26.P$1 (1), D1.C, D2.C, IC5.1 (VIN), IC5.3 (ON/OFF)
+12V: +.1, C17.+, C28.P$1 (1), C29.P$1 (1), C30.P$1 (1), C40.P$1 (1), IC2.1 (VDD), IC3.1 (VDD), IC4.1 (VDD), IC9.1 (VIN), IC9.3 (ON/OFF), Q2.5678D (D), Q4.5678D (D), Q6.5678D (D), R26.P$2 (2)
CAN_H: CJ2.1, IC7.7 (CANH), R20.P$2 (2)
CAN_L: CJ4.1, IC7.6 (CANL), R20.P$1 (1)
CAN_RX: IC1.23 (PA11-USART1CTS/CANRX/USBDM/TIM1CH4), IC7.4 (RXD)
CAN_SLP: IC1.32 (PB5-I2C1SMBAI-TIM3CH2/SPI1MOSI), R12.P$1 (1)
CAN_TX: IC1.24 (PA12-USART1RTS/CANTX/USBDP/TIM1ETR), IC7.1 (TXD)
CTRL_A+: IC1.22 (PA10-USART1RX/TIM1CH3), IC2.7 (HI)
CTRL_A-: IC1.16 (PB1-ADC9/TIM3CH4-TIM1CH3N), IC2.8 (LI)
CTRL_B+: IC1.21 (PA9-USART1TX/TIM1CH2), IC3.7 (HI)
CTRL_B-: IC1.15 (PB0-ADC8/TIM3CH3-TIM1CH2N), IC3.8 (LI)
CTRL_C+: IC1.20 (PA8-USART1CK/TIM1CH1/MCO), IC4.7 (HI)
CTRL_C-: IC1.14 (PA7-SPI1MOSI/ADC7/TIM3CH2-TIM1CH1N), IC4.8 (LI)
GND: -.1, ACS1.5 (GND), ACS2.5 (GND), C1.P$2 (2), C2.P$1 (1), C3.P$2 (2), C4.P$2 (2), C5.P$1 (1), C6.P$1 (1), C7.P$2 (2), C8.P$2 (2), C9.P$2 (2), C10.P$1 (1), C11.P$1 (1), C12.P$1 (1), C13.P$2 (2), C17.-, C19.P$2 (2), C20.P$2 (2), C22.P$2 (2), C23.P$2 (2), C25.P$2 (2), C26.P$2 (2), C28.P$2 (2), C29.P$2 (2), C30.P$2 (2), C40.P$2 (2), IC1.5 (VSSA), IC1.18 (VSS1), IC1.26 (VSS2), IC1.35 (BOOT0), IC1.36 (VSS3), IC2.9 (VSS), IC3.9 (VSS), IC4.9 (VSS), IC5.2 (GND), IC7.2 (GND), IC9.2 (GND), Q1.2 (GND), Q3.123S (S), Q5.123S (S), Q7.123S (S), R6.P$2 (2), R8.P$2 (2), R10.P$2 (2), R19.P$1 (1), R27.P$1 (1), R42.P$2 (2), R44.P$2 (2), X1.1, X2.3, X2.5, X2.7, X2.9
I_A: IC1.13 (PA6-SPI1MISO/ADC6/TIM3CH1-TIM1BKIN), R41.P$1 (1), R42.P$1 (1)
I_B: IC1.11 (PA4-SPI1NSS/ADC4/USART2CK), R43.P$1 (1), R44.P$1 (1)
I_PHASE_A: ACS1.3 (IP-_1), ACS1.4 (IP-_2), PHASE-A.1
I_PHASE_B: ACS2.3 (IP-_1), ACS2.4 (IP-_2), PHASE-B.1
LEDA: IC1.31 (PB4/JNTRST-TIM3CH1/SPI1MISO), R4.P$1 (1)
LEDB: IC1.17 (PB2/BOOT1), R1.P$1 (1)
LEDG: IC1.7 (PA0-WKUP/USART2CTS/ADC0/TIM2CH1_ETR), R3.P$1 (1)
LEDR: IC1.3 (PD1-OSC_OUT), R2.P$1 (1)
LOCAL_+5V: D1.A, IC9.5 (VOUT)
LOU: C2.P$2 (2), C3.P$1 (1), C5.P$2 (2), C7.P$1 (1), C8.P$1 (1), C9.P$1 (1), C10.P$2 (2), C11.P$2 (2), C12.P$2 (2), C25.P$1 (1), IC1.1 (VDD3), IC1.6 (VDDA), IC1.19 (VDD1), IC1.27 (VDD2), IC5.5 (VOUT), IC7.3 (VCC), LEDA.A, LEDB.A, LEDG.A, LEDR.A, Q1.4 (VDD), X2.1
unnamed: IC3.3 (HO), R22.P$1 (1)
unnamed: IC2.3 (HO), R17.P$1 (1)
unnamed: LEDB.C, R1.P$2 (2)
unnamed: C4.P$1 (1), IC5.4 (BYPASS)
unnamed: LEDG.C, R3.P$2 (2)
unnamed: C13.P$1 (1), IC9.4 (BYPASS)
unnamed: IC2.10 (LO), R18.P$1 (1)
unnamed: IC7.8 (RS), R12.P$2 (2)
unnamed: CJ3.2, CJ4.2, X1.3
unnamed: LEDR.C, R2.P$2 (2)
unnamed: Q2.4G (G), R17.P$2 (2)
unnamed: C14.P$1 (1), IC2.2 (HB)
unnamed: IC3.10 (LO), R23.P$1 (1)
unnamed: Q4.4G (G), R22.P$2 (2)
unnamed: Q6.4G (G), R25.P$2 (2)
unnamed: C15.P$1 (1), IC3.2 (HB)
unnamed: Q5.4G (G), R23.P$2 (2)
unnamed: IC4.3 (HO), R25.P$1 (1)
unnamed: IC4.10 (LO), R28.P$1 (1)
unnamed: C16.P$1 (1), IC4.2 (HB)
unnamed: LEDA.C, R4.P$2 (2)
unnamed: CJ1.2, CJ2.2, X1.2
unnamed: Q7.4G (G), R28.P$2 (2)
unnamed: ACS1.6 (FILTER), C20.P$1 (1)
unnamed: ACS1.7 (VIOUT), R41.P$2 (2)
unnamed: ACS2.6 (FILTER), C23.P$1 (1)
unnamed: ACS2.7 (VIOUT), R43.P$2 (2)
unnamed: IC1.2 (PD0-OSC_IN), Q1.3 (OUT)
unnamed: Q3.4G (G), R18.P$2 (2)
PHASE_A: ACS1.1 (IP+_1), ACS1.2 (IP+_2), C14.P$2 (2), IC2.4 (HS), Q2.123S (S), Q3.5678D (D), R5.P$1 (1)
PHASE_B: ACS2.1 (IP+_1), ACS2.2 (IP+_2), C15.P$2 (2), IC3.4 (HS), Q4.123S (S), Q5.5678D (D), R7.P$1 (1)
PHASE_C: C16.P$2 (2), IC4.4 (HS), PHASE-C.1, Q6.123S (S), Q7.5678D (D), R9.P$1 (1)
RST: C6.P$2 (2), IC1.4 (NRST), X2.10
SCL/TXD: CJ1.1, IC1.33 (PB6-I2C1SCL/TIM4CH1-USART1TX), R19.P$2 (2)
SDA/RXD: CJ3.1, IC1.34 (PB7-I2C1SDA/TIM4CH2-USART1RX)
TCK: IC1.28 (PA14-JTCK/SWCLK), X2.4
TDI: IC1.29 (PA15-JTDI-TIM2CH1ETR/SPI1NSS), X2.8
TDO: IC1.30 (PB3/JTDO-TIM2CH2/TRACESWO/SPI1SCK), X2.6
TMS: IC1.25 (PA13-JTMS/SWDIO), X2.2
USART_+5V: D2.A, X1.4
V_A: IC1.12 (PA5-SPI1SCK/ADC5), R5.P$2 (2), R6.P$1 (1)
V_B: IC1.10 (PA3-USART2RX/ADC3/TIM2CH4), R7.P$2 (2), R8.P$1 (1)
V_BATT: IC1.8 (PA1-USART2RTS/ADC1/TIM2CH2), R26.P$1 (1), R27.P$2 (2)
V_C: IC1.9 (PA2-USART2TX/ADC2/TIM2CH3), R9.P$2 (2), R10.P$1 (1)

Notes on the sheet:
License: CC-BY-SA 3.0 DE
http://creativecommons.org/licenses/by-sa/3.0/de/
open-bldc (C) 2008-2009 Piotr Esden-Tempski <piotr at esden.net>
R12 selects the CAN transceiver operation modes:
0Ohm: High speed
10kOhm - 100kOhm: Slew rate control
10kOhm: 15V/us
100kOhm: 2V/us

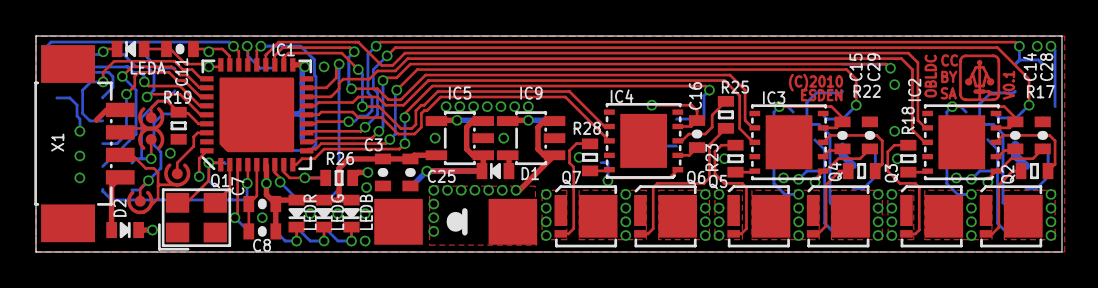
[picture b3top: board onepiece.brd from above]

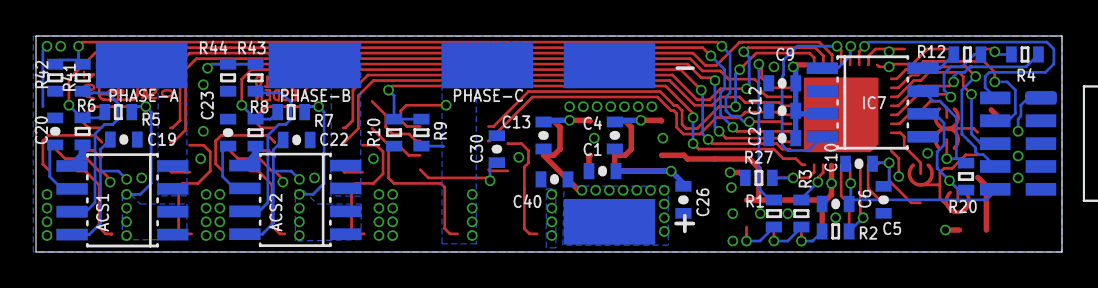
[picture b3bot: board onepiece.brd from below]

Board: 4 copper layers, 57.0 x 12.0 mm, 86 parts (42 on the bottom side), 68 nets.

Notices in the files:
clogic/v1.1/clogic.brd:
(C) 2011 J.R.
cpico_power/v0.1/cpico_power.brd:
(C) 2011 ESDEN
